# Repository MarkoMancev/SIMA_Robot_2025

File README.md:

# SIMA_Robot_2025
Projektovanje SIMA robota za takmičenje Eurobot 2025

**3D prikaz SIMA robota**

**Alati**: Fusion 360

Front view | Back view

Projektovanje i implementacija PCB pločice

**Alati**: KiCad

**MCU**: STM32F401CCU6 Blackpill

PCB pločica | Implementacija pločice u SIMA robota

**Gornji** prikaz povezivanja pločice:

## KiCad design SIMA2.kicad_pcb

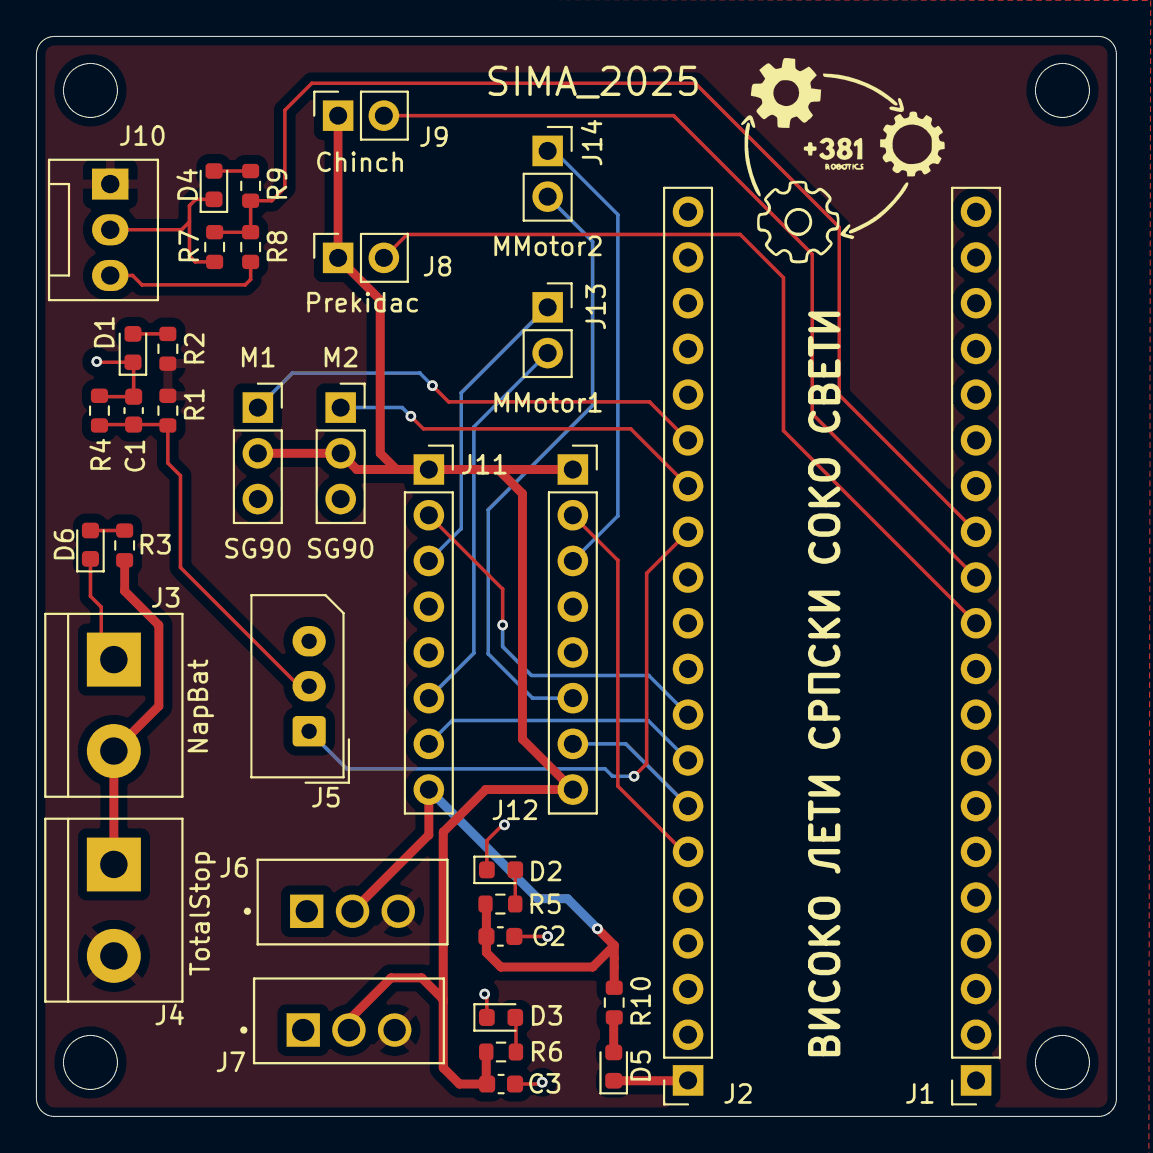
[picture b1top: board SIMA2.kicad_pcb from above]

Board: 2 copper layers, 60.0 x 60.0 mm, 35 parts (0 on the bottom side), 28 nets.

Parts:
C1, C2, C3: 100nF; C_0603_1608Metric
D1, D6: LED; D_0603_1608Metric
D2, D3, D4, D5: 0603; D_0603_1608Metric
J1: STM32-L; PinSocket_1x20_P2.54mm_Vertical
J2: STM32-D; PinSocket_1x20_P2.54mm_Vertical
J3: NapBat; TerminalBlock_bornier-2_P5.08mm
J4: TotalStop; TerminalBlock_bornier-2_P5.08mm
J5: AX_con; Molex_SPOX_5267-03A_1x03_P2.50mm_Vertical
J6, J7: Buck 5V; LM1084-5
J8: Prekidac; PinSocket_1x02_P2.54mm_Vertical
J9: Chinch; PinSocket_1x02_P2.54mm_Vertical
J10: IR senzor; FanPinHeader_1x03_P2.54mm_Vertical
J11: L293D-L; PinSocket_1x08_P2.54mm_Vertical
J12: L293D-D; PinSocket_1x08_P2.54mm_Vertical
J13: MMotor1; PinSocket_1x02_P2.54mm_Vertical
J14: MMotor2; PinSocket_1x02_P2.54mm_Vertical
M1, M2: SG90; PinSocket_1x03_P2.54mm_Vertical
R1, R9: 100R; R_0603_1608Metric
R2, R3: 600R; R_0603_1608Metric
R4: 2k; R_0603_1608Metric
R5, R6: 330R; R_0603_1608Metric
R7: 2k2; R_0603_1608Metric
R8: 4k7; R_0603_1608Metric
R10: 250R; R_0603_1608Metric

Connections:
5VMC_1: D5.1 (K), J2.1
5V_1: C3.1, J7.2, J8.1, J9.1, J11.1, J12.1, J12.8, M1.2 (+), M2.2 (+), R6.1
5V_2: C2.1, J6.2, J11.8, R5.1, R10.2
GND: C1.2, C2.2, C3.2, D1.1 (K), D2.1 (K), D3.1 (K), D4.1 (K), D6.1 (K), J1.19, J2.2, J3.1, J5.3, J6.1, J7.1, J10.2, J11.4, J11.5, J12.4, J12.5, M1.3 (-), M2.3 (-), R4.1, R7.2
unnamed: D1.2 (A), R2.2
unnamed: D2.2 (A), R5.2
unnamed: D3.2 (A), R6.2
unnamed: D4.2 (A), R9.2
unnamed: D5.2 (A), R10.1
unnamed: D6.2 (A), R3.2
unnamed: C1.1, J5.2, R1.1, R4.2
unnamed: J10.3, R8.1
unnamed: J11.3, J13.1
unnamed: J11.6, J13.2
unnamed: J12.3, J14.1
unnamed: J12.6, J14.2
PA0: J2.15, M1.1 (PWM)
PA1: J2.14, M2.1 (PWM)
PA2: J2.13, J5.1
PA6: J2.9, J11.2
PA7: J2.8, J11.7
PB0: J2.7, J12.7
PB1: J2.6, J12.2
PB3: J1.11, J8.2
PB4: J1.12, J9.2
PB5: J1.13, R7.1, R8.2, R9.1
Vbat: J4.2, J6.3, J7.3, J10.1, R1.2, R2.1
Vin: J3.2, J4.1, R3.1

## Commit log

2026-02-20 SIMA PCB
